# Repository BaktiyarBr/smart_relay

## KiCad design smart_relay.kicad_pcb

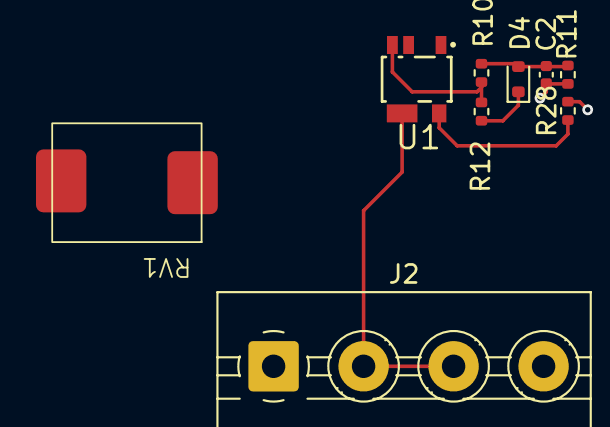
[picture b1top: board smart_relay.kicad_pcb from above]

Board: 2 copper layers, 9 parts (0 on the bottom side), 6 nets.

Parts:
C2: C; C_0402_1005Metric
D4: T4; D_SOD-523
J2: Screw_Terminal_01x04; TerminalBlock_MaiXu_MX126-5.0-04P_1x04_P5.00mm
R10, R11: 0; R_0402_1005Metric
R12: R; R_0402_1005Metric
R28: R11; R_0402_1005Metric
RV1: R_Variable; Untitled
U1: BP8005; SOT33-5B_L3.9-W2.6-P0.90-LS4.0-BL

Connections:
unnamed: C2.1, D4.2 (A), R10.1, R11.1
unnamed: D4.1 (K), R12.2
unnamed: J2.2, J2.3, RV1.2, U1.4 (GND)
unnamed: R10.2, R12.1, U1.3 (GATE)
unnamed: R28.1, U1.5 (RST)
mosfet_gate: C2.2, R11.2

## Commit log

2025-03-05 first
2025-03-05 Auto commit: 2025-03-06_00-34
2025-03-06 Auto commit: 2025-03-07_01-56
2025-03-07 Auto commit: 2025-03-08_02-13
2025-03-10 Auto commit: 2025-03-11_00-25
2025-03-12 Auto commit: 2025-03-12_11-56
2025-03-23 Auto commit: 2025-03-24_00-37
2025-03-27 Auto commit: 2025-03-27_21-00
